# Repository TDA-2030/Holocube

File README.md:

# Holocubic

用 ESP32-S3 重新设计的版本

## 板载资源

- [ESP32-S3FN8 / ESP32-S3FH4R2](https://www.espressif.com/sites/default/files/documentation/esp32-s3_datasheet_en.pdf)
- [WM8978](https://pdf1.alldatasheet.com/datasheet-pdf/view/96647/WOLFSON/WM8978.html) 音频 Codec
- 单声道模拟麦克风
- MPU6050 惯性传感器

## PCB

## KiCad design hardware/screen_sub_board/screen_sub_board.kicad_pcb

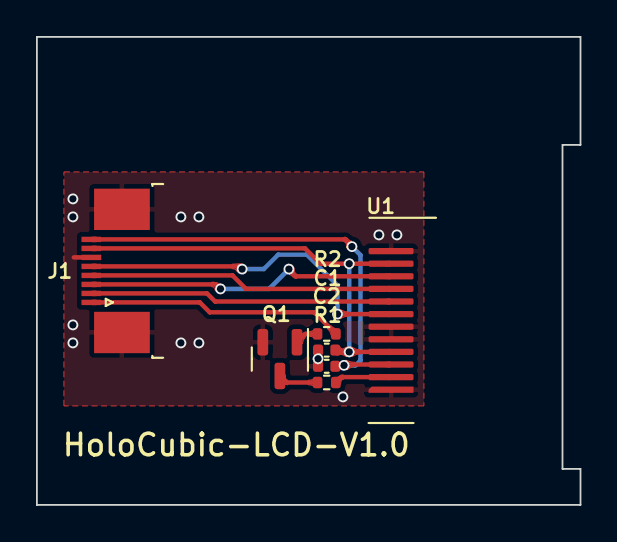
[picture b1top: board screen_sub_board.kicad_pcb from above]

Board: 2 copper layers, 30.2 x 26.0 mm, 7 parts (0 on the bottom side), 11 nets.

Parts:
C1, C2: 1uf; C_0402_1005Metric
J1: Conn_01x08_MountingPin; TE_0-1734839-8_1x08-1MP_P0.5mm_Horizontal
Q1: S8050; SOT-23
R1: 22R; R_0402_1005Metric
R2: 10K; R_0402_1005Metric
U1: LCD_1.3_240x240_ST7789

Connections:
+3V3: C1.1, J1.7, U1.4 (VDD), U1.11 (RST)
+5V: C2.1, J1.8, U1.3 (LEDA)
/BL: J1.1, R2.2
/CS: J1.2, U1.8 (CS)
/DC: J1.5, U1.7 (DC)
/MOSI: J1.3, U1.10 (SDA)
/SCLK: J1.4, U1.9 (SCL)
GND: C1.2, C2.2, J1.6, J1.MP (MountPin), Q1.2 (E), U1.1 (GND), U1.5 (GND), U1.6 (GND), U1.12 (GND)
unnamed: R1.1, U1.2 (LEDK)
unnamed: Q1.3 (C), R1.2
unnamed: Q1.1 (B), R2.1

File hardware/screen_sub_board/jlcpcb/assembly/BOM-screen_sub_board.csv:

Comment,Designator,Footprint,LCSC
S8050,Q1,SOT-23,
22R,R1,R_0402_1005Metric,
Conn_01x08_MountingPin,J1,TE_0-1734839-8_1x08-1MP_P0.5mm_Horizontal,
1uf,C1,C_0402_1005Metric,
LCD_1.3_240x240_ST7789,U1,LCD_1.3_240x240_ST7789,
10K,R2,R_0402_1005Metric,
1uf,C2,C_0402_1005Metric,

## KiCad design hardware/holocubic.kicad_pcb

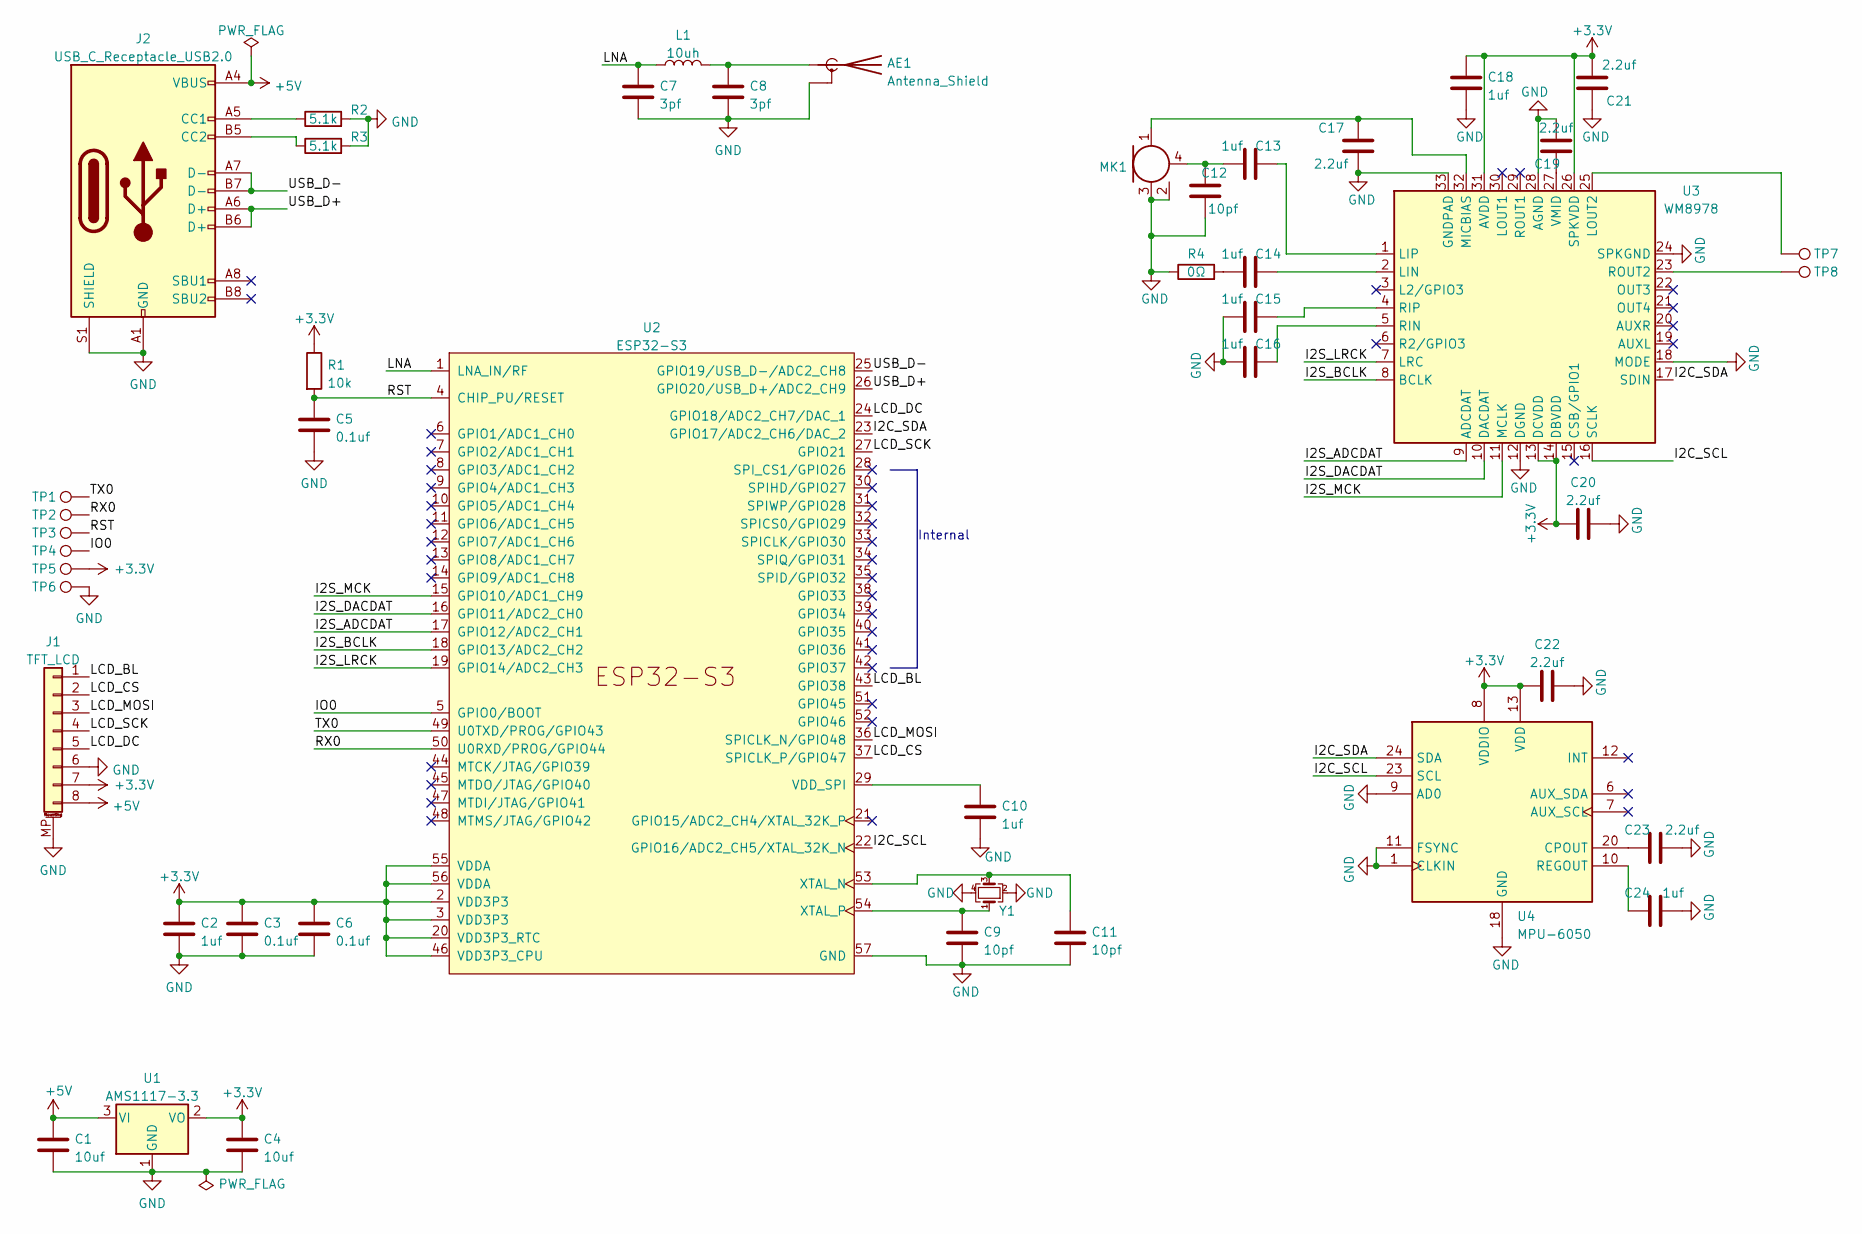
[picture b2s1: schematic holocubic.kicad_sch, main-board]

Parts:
AE1: Antenna_Shield; Texas_SWRA117D_2.4GHz_Left
C1, C4: 10uf; C_0603_1608Metric
C2: 1uf; C_0603_1608Metric
C3, C5, C6: 0.1uf; C_0402_1005Metric
C7, C8: 3pf; C_0402_1005Metric
C9, C11, C12: 10pf; C_0402_1005Metric
C10, C13, C14, C15, C16, C18, C24: 1uf; C_0402_1005Metric
C17, C19, C20, C21, C22, C23: 2.2uf; C_0402_1005Metric
J1: TFT_LCD; TE_0-1734839-8_1x08-1MP_P0.5mm_Horizontal
J2: USB_C_Receptacle_USB2.0; USB_C_Receptacle_HRO_TYPE-C-31-M-12
L1: 10uh; L_0402_1005Metric
MK1: Microphone_MEMS; MEMS_MIC_2.75x1.85x0.9mm
R1: 10k; R_0402_1005Metric
R2, R3: 5.1k; R_0402_1005Metric
R4: 0Ω; R_0402_1005Metric
TP1, TP2, TP3, TP4, TP5, TP6, TP7, TP8: TestPoint; TestPoint_Pad_D1.0mm
U1: AMS1117-3.3; SOT-223-3_TabPin2
U2: ESP32-S3; QFN-56-1EP_7x7mm_P0.4mm_EP5.6x5.6mm
U3: WM8978; QFN-32-1EP_5x5mm_P0.5mm_EP3.3x3.3mm
U4: MPU-6050; InvenSense_QFN-24_4x4mm_P0.5mm
Y1: 40MHz; Crystal_SMD_3225-4Pin_3.2x2.5mm

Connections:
/I2C_SCL: U2.22 (GPIO16/ADC2_CH5/XTAL_32K_N), U3.16 (SCLK), U4.23 (SCL)
/I2C_SDA: U2.23 (GPIO17/ADC2_CH6/DAC_2), U3.17 (SDIN), U4.24 (SDA)
/I2S_ADCDAT: U2.17 (GPIO12/ADC2_CH1), U3.9 (ADCDAT)
/I2S_BCLK: U2.18 (GPIO13/ADC2_CH2), U3.8 (BCLK)
/I2S_DACDAT: U2.16 (GPIO11/ADC2_CH0), U3.10 (DACDAT)
/I2S_LRCK: U2.19 (GPIO14/ADC2_CH3), U3.7 (LRC)
/I2S_MCK: U2.15 (GPIO10/ADC1_CH9), U3.11 (MCLK)
/IO0: TP4.1, U2.5 (GPIO0/BOOT)
/LCD_BL: J1.1, U2.43 (GPIO38)
/LCD_CS: J1.2, U2.37 (SPICLK_P/GPIO47)
/LCD_DC: J1.5, U2.24 (GPIO18/ADC2_CH7/DAC_1)
/LCD_MOSI: J1.3, U2.36 (SPICLK_N/GPIO48)
/LCD_SCK: J1.4, U2.27 (GPIO21)
/LNA: C7.1, L1.1, U2.1 (LNA_IN/RF)
/RST: C5.1, R1.2, TP3.1, U2.4 (CHIP_PU/RESET)
/RX0: TP2.1, U2.50 (U0RXD/PROG/GPIO44)
/TX0: TP1.1, U2.49 (U0TXD/PROG/GPIO43)
/USB_D+: J2.A6 (D+), J2.B6 (D+), U2.26 (GPIO20/USB_D+/ADC2_CH9)
/USB_D-: J2.A7 (D-), J2.B7 (D-), U2.25 (GPIO19/USB_D-/ADC2_CH8)
GND: AE1.2 (Shield), C1.2, C2.2, C3.2, C4.2, C5.2, C6.2, C7.2, C8.2, C9.2, C10.2, C11.2, C12.1, C15.1, C16.1, C17.2, C18.2, C19.2, C20.1, C21.1, C22.1, C23.1, C24.1, J1.6, J1.MP (MountPin), J2.A1 (GND), J2.A12 (GND), J2.B1 (GND), J2.B12 (GND), J2.S1 (SHIELD), MK1.2 (GND), MK1.3 (GND), R2.2, R3.2, R4.1, TP6.1, U1.1 (GND), U2.57 (GND), U3.12 (DGND), U3.18 (MODE), U3.24 (SPKGND), U3.28 (AGND), U3.33 (GNDPAD), U4.1 (CLKIN), U4.9 (AD0), U4.11 (FSYNC), U4.18 (GND), Y1.2, Y1.4; also elsewhere on the board
unnamed: AE1.1 (A), C8.1, L1.2
unnamed: C9.1, U2.54 (XTAL_P), Y1.1
unnamed: C10.1, U2.29 (VDD_SPI)
unnamed: C11.1, U2.53 (XTAL_N), Y1.3
unnamed 24: C12.2, C13.1, MK1.4 (OUT); also elsewhere on the board
unnamed: C13.2, U3.1 (LIP)
unnamed: C14.1, R4.2
unnamed: C14.2, U3.2 (LIN)
unnamed: C15.2, U3.4 (RIP)
unnamed: C16.2, U3.5 (RIN)
unnamed 30: C17.1, MK1.1 (VDD), U3.32 (MICBIAS); also elsewhere on the board
unnamed: C19.1, U3.27 (VMID)
unnamed: C23.2, U4.20 (CPOUT)
unnamed: C24.2, U4.10 (REGOUT)
unnamed: J2.A5 (CC1), R2.1
unnamed: J2.B5 (CC2), R3.1
unnamed: TP7.1, U3.25 (LOUT2)
unnamed: TP8.1, U3.23 (ROUT2)

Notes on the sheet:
Internal

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
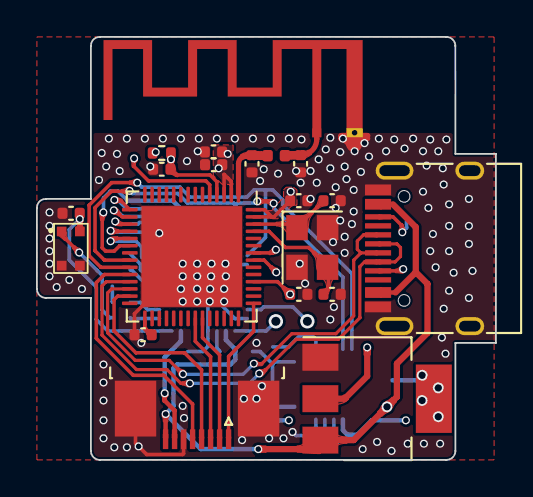
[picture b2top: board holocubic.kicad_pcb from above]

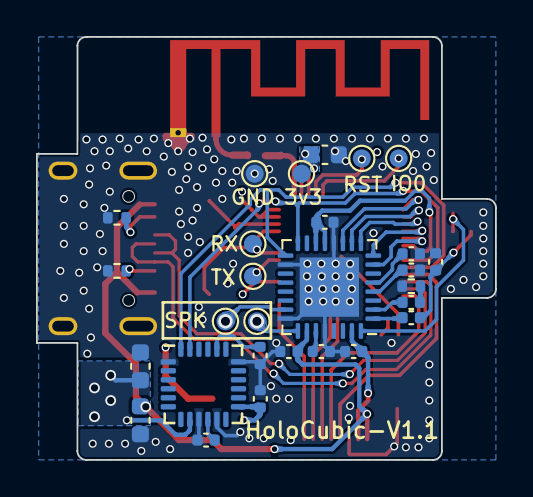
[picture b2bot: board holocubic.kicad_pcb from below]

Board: 4 copper layers, 25.5 x 23.5 mm, 48 parts (28 on the bottom side), 40 nets.

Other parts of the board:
C25: 1uf; C_0402_1005Metric
C26: 0.1uf; C_0402_1005Metric
MK?: Microphone_MEMS; MEMS_MIC_2.75x1.85x0.9mm

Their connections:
GND: C25.1, C26.1, MK?.2 (GND), MK?.3 (GND); also elsewhere on the board
unnamed 24: MK?.4 (OUT); also elsewhere on the board
unnamed 30: MK?.1 (VDD); also elsewhere on the board

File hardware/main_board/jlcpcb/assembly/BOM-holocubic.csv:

Comment,Designator,Footprint,LCSC
1uf,C25,C_0402_1005Metric,
0.1uf,C26,C_0402_1005Metric,
2.2uf,C17,C_0402_1005Metric,
AMS1117-3.3,U1,SOT-223-3_TabPin2,
1uf,C10,C_0402_1005Metric,
Antenna_Shield,AE1,Texas_SWRA117D_2.4GHz_Left,
TBD,C8,C_0402_1005Metric,
TBD,C7,C_0402_1005Metric,
40MHz,Y1,Crystal_SMD_3225-4Pin_3.2x2.5mm,
0.1uf,C3,C_0402_1005Metric,
10pf,C9,C_0402_1005Metric,
10pf,C11,C_0402_1005Metric,
USB_C_Receptacle_USB2.0,J2,USB_C_Receptacle_HRO_TYPE-C-31-M-12,
TBD,L1,L_0402_1005Metric,
ESP32-S3,U2,QFN-56-1EP_7x7mm_P0.4mm_EP5.6x5.6mm,
10uf,C2,C_0603_1608Metric,
TFT_LCD,J1,TE_0-1734839-8_1x08-1MP_P0.5mm_Horizontal,
10k,R1,R_0402_1005Metric,
0.1uf,C5,C_0402_1005Metric,
Microphone_MEMS,MK1,MEMS_MIC_2.75x1.85x0.9mm,
0.1uf,C6,C_0402_1005Metric,
10uf,C4,C_0603_1608Metric,
1uf,C14,C_0402_1005Metric,
2.2uf,C21,C_0402_1005Metric,
TestPoint,TP8,TestPoint_Pad_D1.0mm,
TestPoint,TP7,TestPoint_Pad_D1.0mm,
TestPoint,TP3,TestPoint_Pad_D1.0mm,
0Ω,R4,R_0402_1005Metric,
TestPoint,TP4,TestPoint_Pad_D1.0mm,
2.2uf,C19,C_0402_1005Metric,
WM8978,U3,QFN-32-1EP_5x5mm_P0.5mm_EP3.3x3.3mm,
2.2uf,C23,C_0402_1005Metric,
1uf,C13,C_0402_1005Metric,
5.1k,R2,R_0402_1005Metric,
2.2uf,C20,C_0402_1005Metric,
TestPoint,TP6,TestPoint_Pad_D1.0mm,
TestPoint,TP5,TestPoint_Pad_D1.0mm,
1uf,C15,C_0402_1005Metric,
1uf,C16,C_0402_1005Metric,
10uf,C1,C_0603_1608Metric,
10pf,C12,C_0402_1005Metric,
2.2uf,C22,C_0402_1005Metric,
MPU-6050,U4,InvenSense_QFN-24_4x4mm_P0.5mm,
TestPoint,TP1,TestPoint_Pad_D1.0mm,
5.1k,R3,R_0402_1005Metric,
TestPoint,TP2,TestPoint_Pad_D1.0mm,
1uf,C24,C_0402_1005Metric,
1uf,C18,C_0402_1005Metric,

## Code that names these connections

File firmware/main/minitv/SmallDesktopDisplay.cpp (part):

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 *            V1.4    增加web服务器，使用web网页进行设置。由于使用了web服务器，无法开启WiFi休眠。
 *                    注意，此版本中的DHT11传感器和太空人图片选择可以通过web网页设置来进行选择，无需通过使能标志来重新编译。
 * 
 * 引 脚 分 配： SCK  GPIO14
 *             MOSI  GPIO13
 *             RES   GPIO2
 *             DC    GPIO0
 *             LCDBL GPIO5
 *             
 *             增加DHT11温湿度传感器，传感器接口为 GPIO 12
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      LCD_BL_PWM = EEPROM.read(BL_addr); 
      delay(5);
      Serial.printf("亮度调整为：");
      analogWrite(LCD_BL_PIN, 1023 - (LCD_BL_PWM*10));
      Serial.println(LCD_BL_PWM);
      Serial.println("");
    }
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
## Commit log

2022-01-18 add bin.
2022-01-18 新建 bin
2022-01-18 upload bin files
2022-01-18 删除文件 bin/.keep
2022-01-18 add city code
2022-06-09 add firmware
2022-06-09 hw: update
2022-06-09 add speech recognition
2022-06-09 add board support
2022-06-09 hw: v1.0
2022-06-12 add aio
2022-06-12 update aio
2022-06-12 add arduino-esp32
2022-06-14 update app
2022-06-18 sw: update
2022-06-18 hw: v1.1
2022-06-18 hw: add lcd sub board
2022-06-18 refactor
2022-06-25 update sw
2022-07-22 update sch
